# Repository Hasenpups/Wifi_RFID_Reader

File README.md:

Shield: [![CC BY-NC-SA 4.0][cc-by-nc-sa-shield]][cc-by-nc-sa]

This work is licensed under a
[Creative Commons Attribution-NonCommercial-ShareAlike 4.0 International License][cc-by-nc-sa].

[![CC BY-NC-SA 4.0][cc-by-nc-sa-image]][cc-by-nc-sa]

[cc-by-nc-sa]: http://creativecommons.org/licenses/by-nc-sa/4.0/
[cc-by-nc-sa-image]: https://licensebuttons.net/l/by-nc-sa/4.0/88x31.png
[cc-by-nc-sa-shield]: https://img.shields.io/badge/License-CC%20BY--NC--SA%204.0-lightgrey.svg

## Donations / Spenden
If somebody wants to support me for upcoming projects :)  
- PayPal:  
- Amazon Giftcard: https://www.amazon.de/Amazon-Gutschein-per-E-Mail-Amazon/dp/B0054PDOV8 - stefan.riese@me.com

# RFID WiFi Reader
This RFID WiFi Reader is used to read RFID cards or keychain pendant and send the serial number via MQTT. Additionally there is an option to solder 3 tactile push buttons to the PCB for user inputs. 

## Features
- MQTT interface
- Power options: 
  - Barrel jack
  - USB from Wemos
  - Solder of cables to pads
- 3 Buttons for user input
  - 6x6mm tactile push buttons or soldered to pads or 2,54mm dupont connector
- additional pins from ESP for addons

## BOM
|Id|Designator|Package|Quantity|Designation|Comment|
|---|---|---|---|---|---|
|1|SW1,SW3,SW2|SW_PUSH_6mm_H9.5mm|3|SW_Push|optional||
|2|J1|PinHeader_1x04_P2.54mm_Vertical|1|Conn_01x04_Female|PN532||
|3|R2,R1,R3|R_Axial_DIN0207_L6.3mm_D2.5mm_P7.62mm_Horizontal|3|10K|not used||
|4|J3|PinHeader_1x08_P2.54mm_Horizontal|1|Conn_01x08_Female|optional||
|5|JSW3,JSW2,JSW1|PinHeader_1x02_P2.54mm_Horizontal|3|Conn_01x02_Female|optional||
|6|J2|BarrelJack_Horizontal|1|Barrel_Jack|optional||
|7|U1|WEMOS_D1_mini_light|1|WeMos_D1_mini|||

## Wiring diagram
https://github.com/Hasenpups/Wifi_RFID_Reader/blob/main/RFID_Reader.pdf

## Software
https://espeasy.readthedocs.io/

## Pinout
- PN532 module
  - I2C
    - SCL - D1
    - SDA - D2
- Buttons 
  - D4
  - D5
  - D6

## Configuration

## Housing
https://github.com/Hasenpups/Wifi_RFID_Reader/tree/main/Housing

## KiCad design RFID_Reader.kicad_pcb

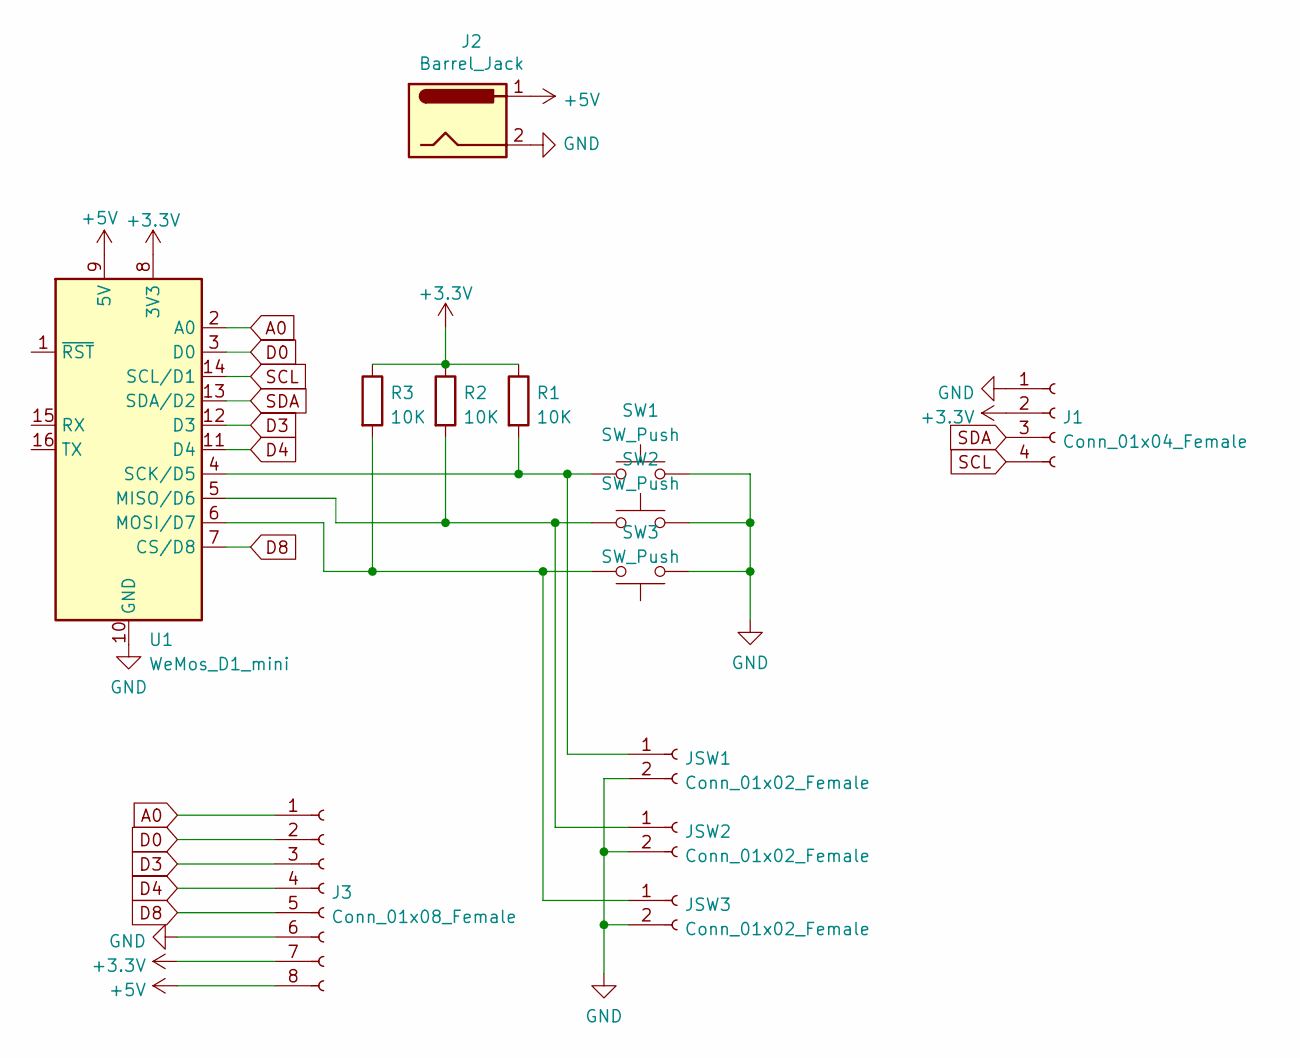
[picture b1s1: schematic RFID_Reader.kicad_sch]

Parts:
J1: Conn_01x04_Female; PinHeader_1x04_P2.54mm_Vertical
J2: Barrel_Jack; BarrelJack_Horizontal
J3: Conn_01x08_Female; PinHeader_1x08_P2.54mm_Horizontal
JSW1, JSW2, JSW3: Conn_01x02_Female; PinHeader_1x02_P2.54mm_Horizontal
R1, R2, R3: 10K; R_Axial_DIN0207_L6.3mm_D2.5mm_P7.62mm_Horizontal
SW1, SW2, SW3: SW_Push; SW_PUSH_6mm_H9.5mm
U1: WeMos_D1_mini; WEMOS_D1_mini_light

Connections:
+3V3: J1.2, J3.7, R1.1, R2.1, R3.1, U1.8 (3V3)
+5V: J2.1, J3.8, U1.9 (5V)
A0: J3.1, U1.2 (A0)
D0: J3.2, U1.3 (D0)
D3: J3.3, U1.12 (D3)
D4: J3.4, U1.11 (D4)
D8: J3.5, U1.7 (CS/D8)
GND: J1.1, J2.2, J3.6, JSW1.2, JSW2.2, JSW3.2, SW1.2, SW2.2, SW3.1, U1.10 (GND)
unnamed: JSW1.1, R1.2, SW1.1, U1.4 (SCK/D5)
unnamed: JSW2.1, R2.2, SW2.1, U1.5 (MISO/D6)
unnamed: JSW3.1, R3.2, SW3.2, U1.6 (MOSI/D7)
SCL: J1.4, U1.14 (SCL/D1)
SDA: J1.3, U1.13 (SDA/D2)

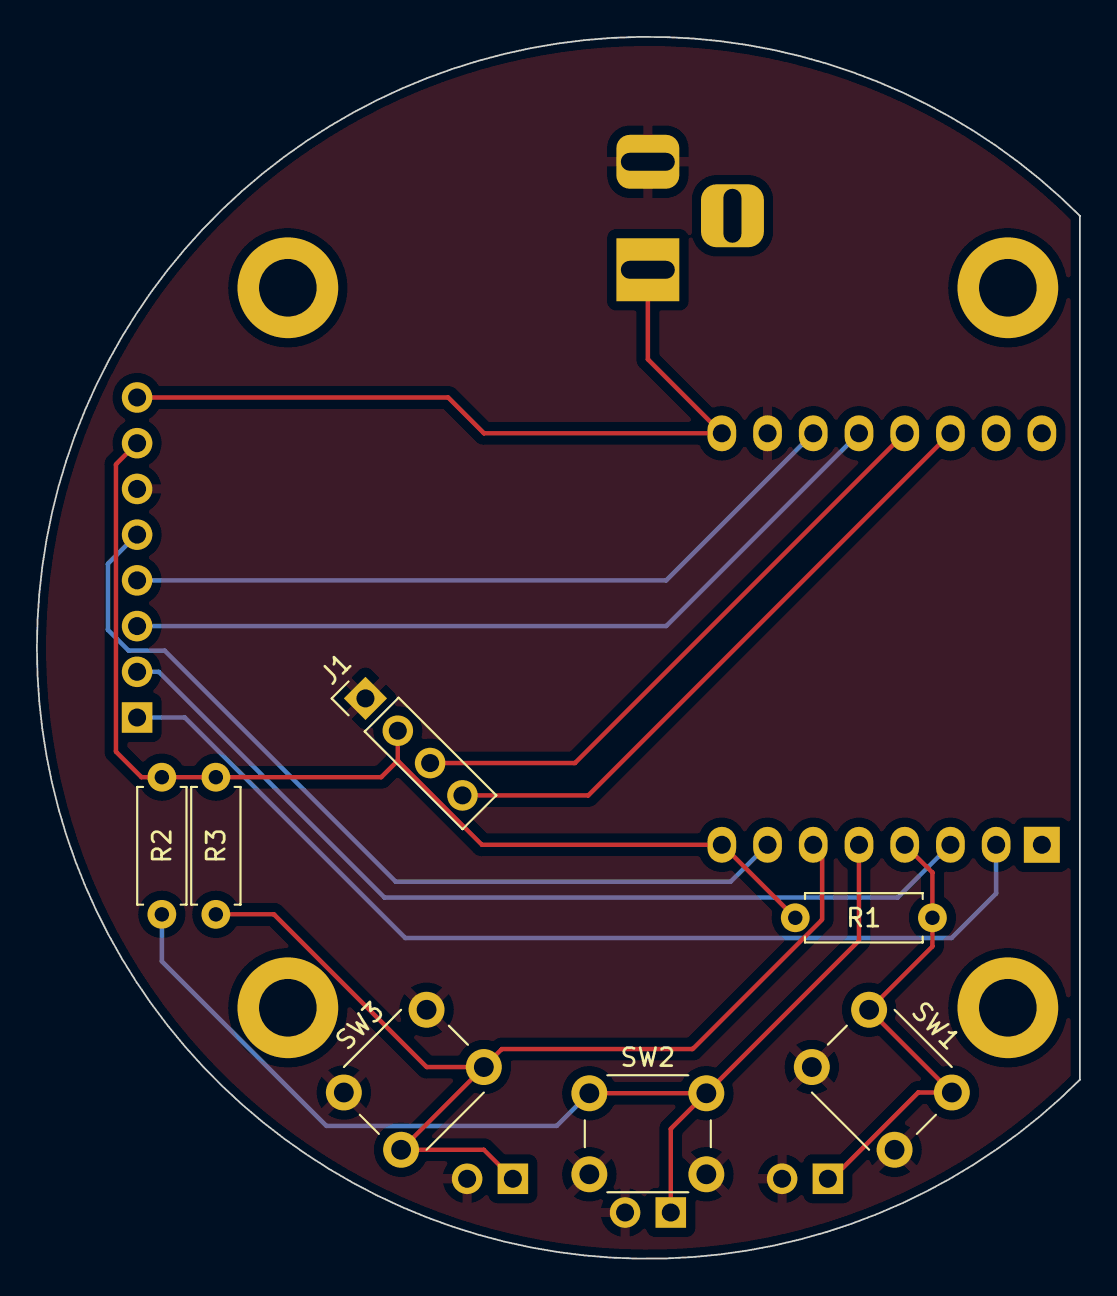
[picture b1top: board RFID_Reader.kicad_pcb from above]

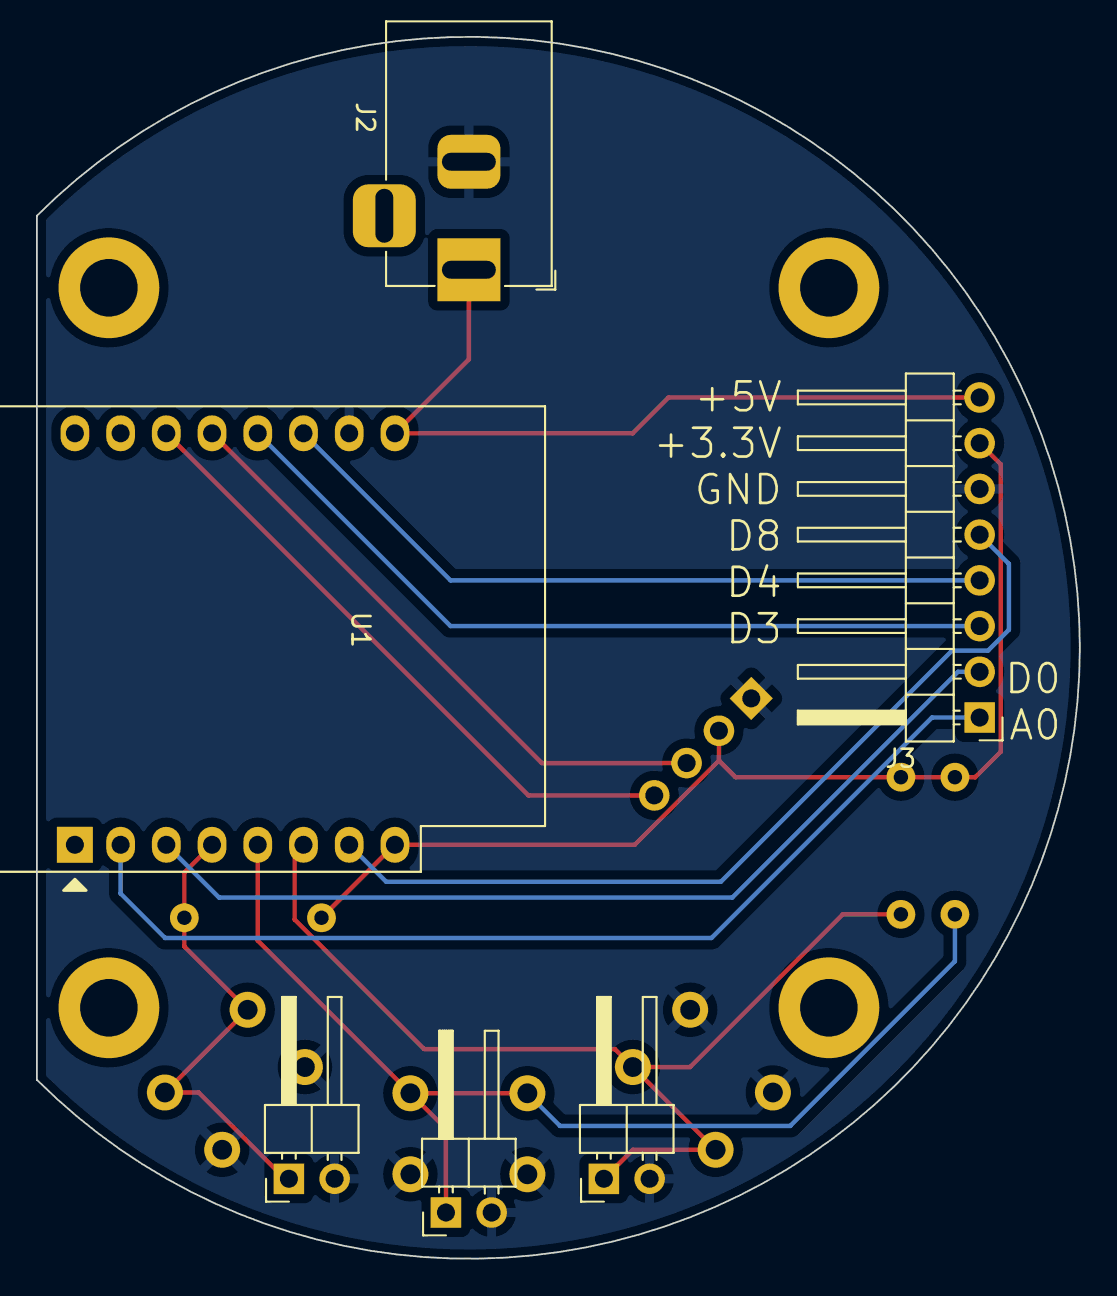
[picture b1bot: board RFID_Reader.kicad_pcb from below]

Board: 2 copper layers, 57.9 x 67.9 mm, 17 parts (6 on the bottom side), 13 nets.

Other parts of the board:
Hole1, Hole2, Hole3, Hole4: MountingHole_3.2mm_M3_DIN965_Pad

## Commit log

2022-06-08 - initial commit
2022-06-21 - add bom, step and schematic as PDF
2022-06-21 - add Housing
2022-06-21 add images
2023-03-12 Create File
